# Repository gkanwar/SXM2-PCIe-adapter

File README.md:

# SXM2-PCIe-adapter

This project builds on [preliminary work](http://github.com/bbenchoff/SXM2toPCIe) by Brian Benchoff
to set up an open-hardware SXM2 to PCIe adapter module.

# Status
Board setup and impedance calculations are done. Differential pairs routing nearly finished:

# Todo list
 - [x] Set up PCB stackup consistent with JLCPCB 4-layer impedance-controlled options
 - [ ] Route differential pairs
 - [ ] Place ground vias / stitching
 - [ ] Add 12V 2x6 power management, routed into SXM directly
 - [ ] Place needed screw holes for heat sink and fan

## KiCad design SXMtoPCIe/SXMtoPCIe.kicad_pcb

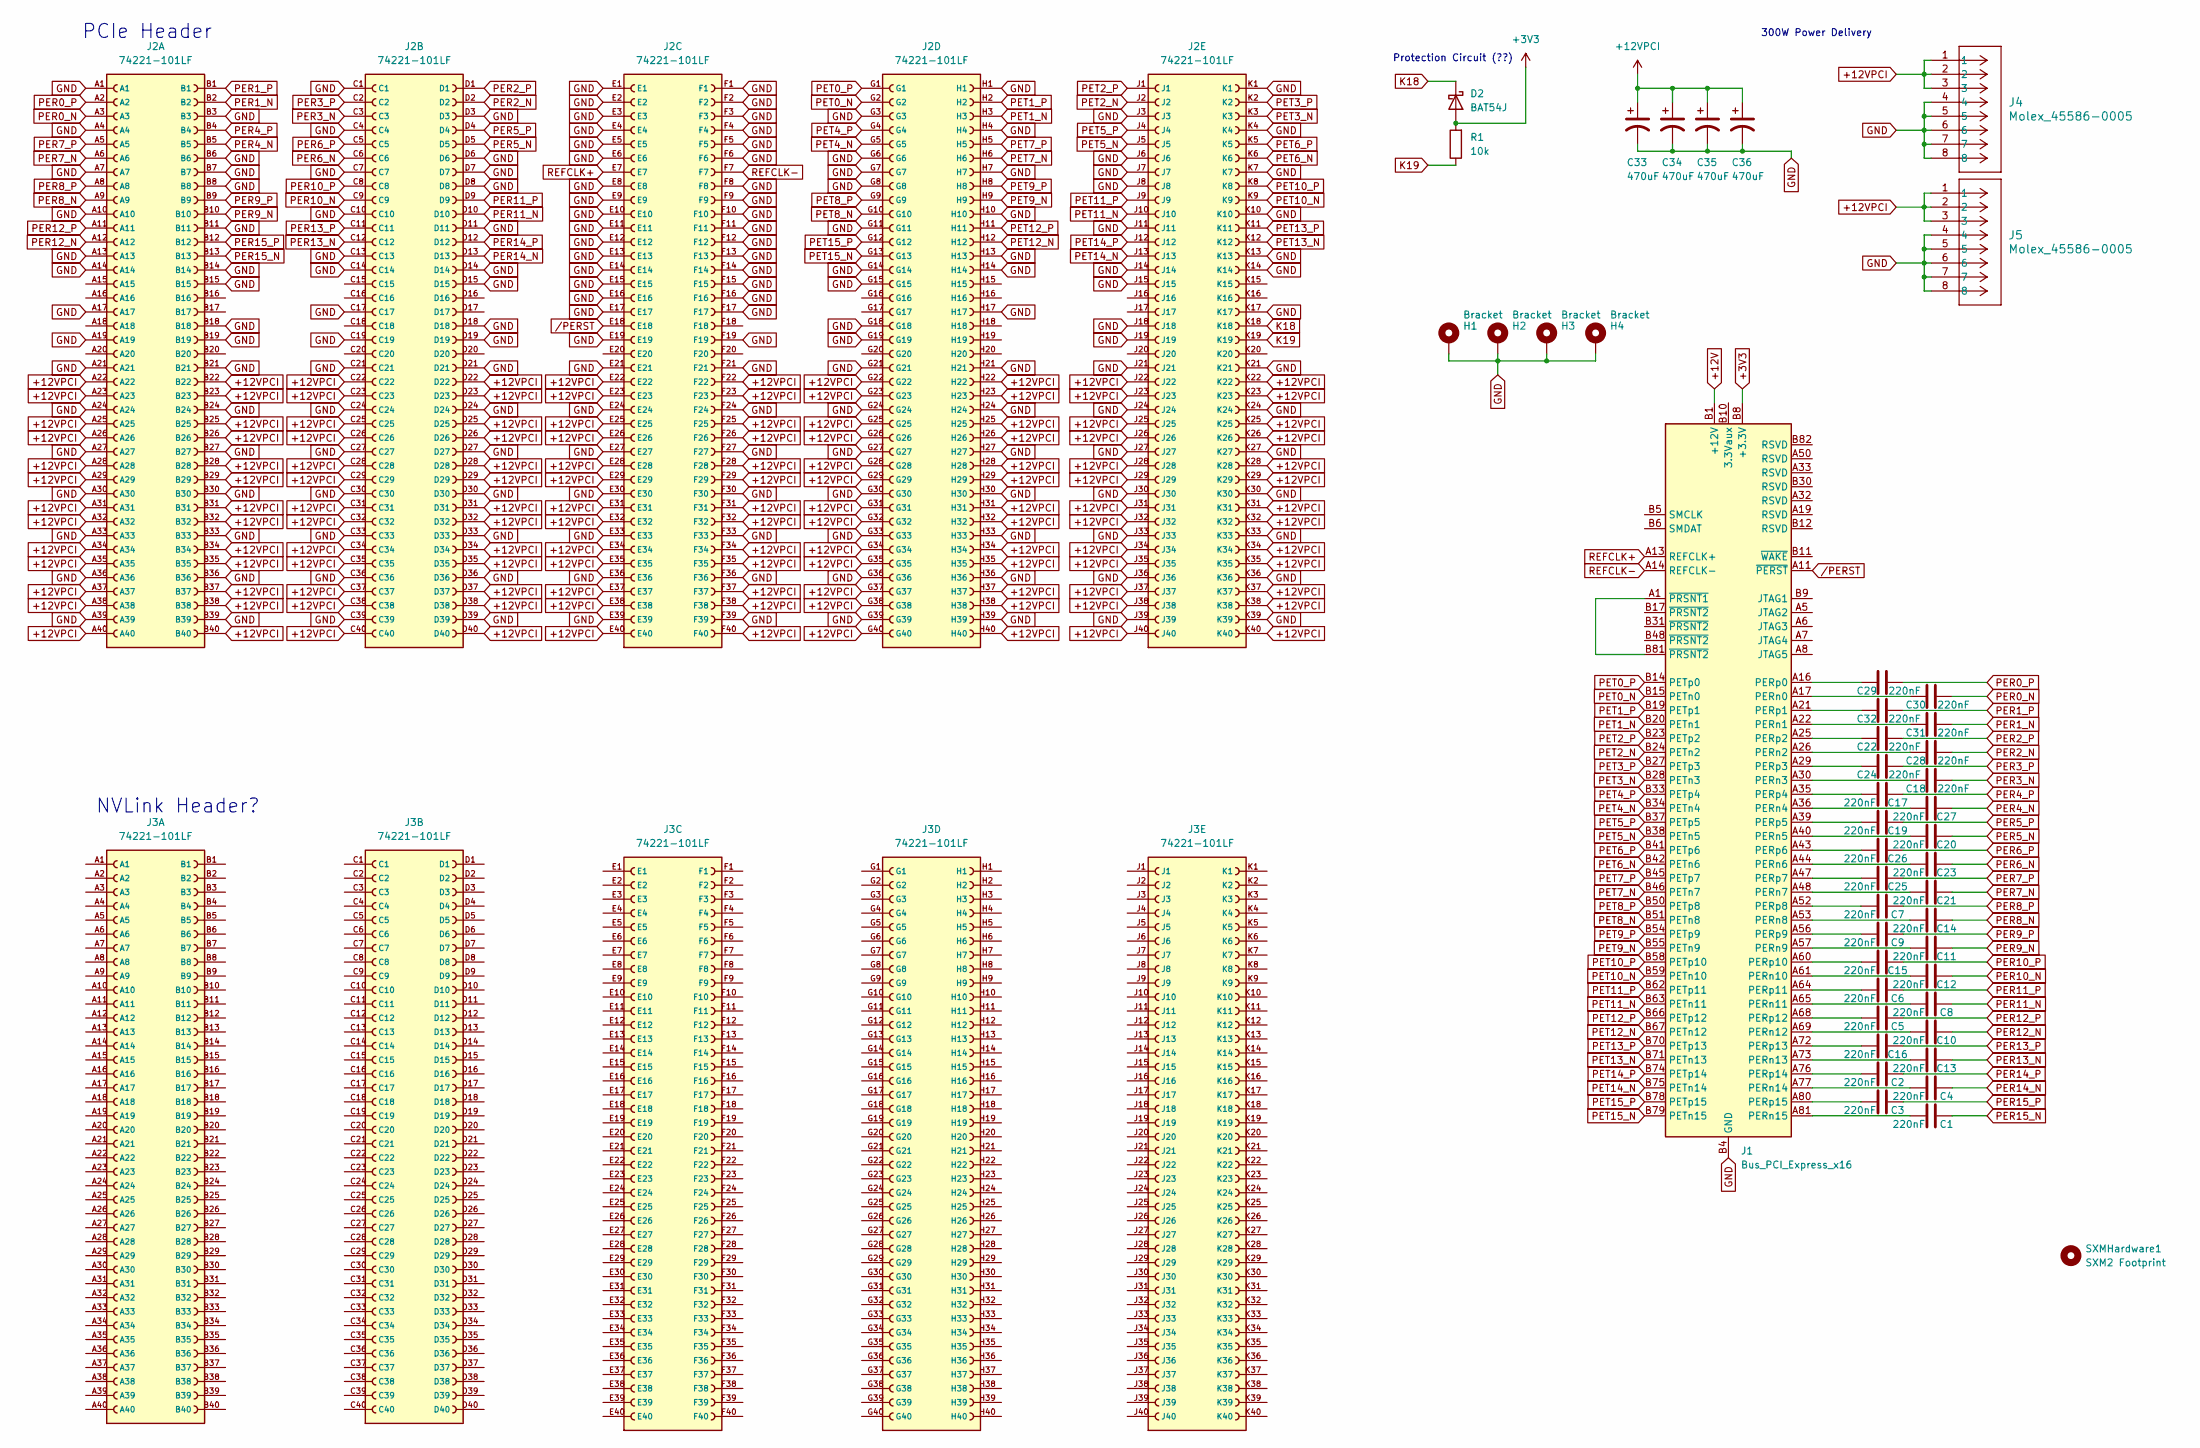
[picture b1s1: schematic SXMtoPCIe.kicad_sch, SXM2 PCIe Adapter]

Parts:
C1, C2, C3, C4, C5, C6, C7, C8, C9, C10, C11, C12, C13, C14, C15, C16, C17, C18, C19, C20, C21, C22, C23, C24, C25, C26, C27, C28, C29, C30, C31, C32: 220nF; C_0201_0603Metric_Pad0.64x0.40mm_HandSolder
C33, C34, C35, C36: 470uF; CP_Elec_6.3x7.7
D2: BAT54J; D_SOD-123
H1, H2, H3, H4: Bracket; MountingHole_3.2mm_M3_Pad_Via
J1: Bus_PCI_Express_x16; BUS_PCIexpress_x16
J2, J3: 74221-101LF; AMPHENOL_74221-101LF; PARTREV W
J4, J5: Molex_45586-0005; CONN_455860000-SD_MOL
R1: 10k; R_0402_1005Metric_Pad0.72x0.64mm_HandSolder
SXMHardware1: SXM2 Footprint; SXM2-Hardware; Digikey Part 78614040360 (times 8)

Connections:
+3V3: D2.2 (A), J1.A9 (+3.3V), J1.A10 (+3.3V), J1.B8 (+3.3V), R1.2
+12V: J1.A2 (+12V), J1.A3 (+12V), J1.B1 (+12V), J1.B2 (+12V), J1.B3 (+12V)
+12VPCI: C33.1, C34.1, C35.1, C36.1, J2.A22, J2.A23, J2.A25, J2.A26, J2.A28, J2.A29, J2.A31, J2.A32, J2.A34, J2.A35, J2.A37, J2.A38, J2.A40, J2.B22, J2.B23, J2.B25, J2.B26, J2.B28, J2.B29, J2.B31, J2.B32, J2.B34, J2.B35, J2.B37, J2.B38, J2.B40, J2.C22, J2.C23, J2.C25, J2.C26, J2.C28, J2.C29, J2.C31, J2.C32, J2.C34, J2.C35, J2.C37, J2.C38, J2.C40, J2.D22, J2.D23, J2.D25, J2.D26, J2.D28, J2.D29, J2.D31, J2.D32, J2.D34, J2.D35, J2.D37, J2.D38, J2.D40, J2.E22, J2.E23, J2.E25, J2.E26, J2.E28, J2.E29, J2.E31, J2.E32, J2.E34, J2.E35, J2.E37, J2.E38, J2.E40, J2.F22, J2.F23, J2.F25, J2.F26, J2.F28, J2.F29, J2.F31, J2.F32, J2.F34, J2.F35, J2.F37, J2.F38, J2.F40, J2.G22, J2.G23, J2.G25, J2.G26, J2.G28, J2.G29, J2.G31, J2.G32, J2.G34, J2.G35, J2.G37, J2.G38, J2.G40, J2.H22, J2.H23, J2.H25, J2.H26, J2.H28, J2.H29, J2.H31, J2.H32, J2.H34, J2.H35, J2.H37, J2.H38, J2.H40, J2.J22, J2.J23, J2.J25, J2.J26, J2.J28, J2.J29, J2.J31, J2.J32, J2.J34, J2.J35, J2.J37, J2.J38, J2.J40, J2.K22, J2.K23, J2.K25, J2.K26, J2.K28, J2.K29, J2.K31, J2.K32, J2.K34, J2.K35, J2.K37, J2.K38, J2.K40, J4.1, J4.2, J4.3, J5.1, J5.2, J5.3
GND: C33.2, C34.2, C35.2, C36.2, H1.1 (1_1), H2.1 (1_1), H3.1 (1_1), H4.1 (1_1), J1.A4 (GND), J1.A12 (GND), J1.A15 (GND), J1.A18 (GND), J1.A20 (GND), J1.A23 (GND), J1.A24 (GND), J1.A27 (GND), J1.A28 (GND), J1.A31 (GND), J1.A34 (GND), J1.A37 (GND), J1.A38 (GND), J1.A41 (GND), J1.A42 (GND), J1.A45 (GND), J1.A46 (GND), J1.A49 (GND), J1.A51 (GND), J1.A54 (GND), J1.A55 (GND), J1.A58 (GND), J1.A59 (GND), J1.A62 (GND), J1.A63 (GND), J1.A66 (GND), J1.A67 (GND), J1.A70 (GND), J1.A71 (GND), J1.A74 (GND), J1.A75 (GND), J1.A78 (GND), J1.A79 (GND), J1.A82 (GND), J1.B4 (GND), J1.B7 (GND), J1.B13 (GND), J1.B16 (GND), J1.B18 (GND), J1.B21 (GND), J1.B22 (GND), J1.B25 (GND), J1.B26 (GND), J1.B29 (GND), J1.B32 (GND), J1.B35 (GND), J1.B36 (GND), J1.B39 (GND), J1.B40 (GND), J1.B43 (GND), J1.B44 (GND), J1.B47 (GND), J1.B49 (GND), J1.B52 (GND), J1.B53 (GND), J1.B56 (GND), J1.B57 (GND), J1.B60 (GND), J1.B61 (GND), J1.B64 (GND), J1.B65 (GND), J1.B68 (GND), J1.B69 (GND), J1.B72 (GND), J1.B73 (GND), J1.B76 (GND), J1.B77 (GND), J1.B80 (GND), J2.A1, J2.A4, J2.A7, J2.A10, J2.A13, J2.A14, J2.A17, J2.A19, J2.A21, J2.A24, J2.A27, J2.A30, J2.A33, J2.A36, J2.A39, J2.B3, J2.B6, J2.B7, J2.B8, J2.B11, J2.B14, J2.B15, J2.B18, J2.B19, J2.B21, J2.B24, J2.B27, J2.B30, J2.B33, J2.B36, J2.B39, J2.C1, J2.C4, J2.C7, J2.C10, J2.C13, J2.C14, J2.C17, J2.C19, J2.C21, J2.C24, J2.C27, J2.C30, J2.C33, J2.C36, J2.C39, J2.D3, J2.D6, J2.D7, J2.D8, J2.D11, J2.D14, J2.D15, J2.D18, J2.D19, J2.D21, J2.D24, J2.D27, J2.D30, J2.D33, J2.D36, J2.D39, J2.E1, J2.E2, J2.E3, J2.E4, J2.E5, J2.E6, J2.E8, J2.E9, J2.E10, J2.E11, J2.E12, J2.E13, J2.E14, J2.E15, J2.E16, J2.E17, J2.E19, J2.E21, J2.E24, J2.E27, J2.E30, J2.E33, J2.E36, J2.E39, J2.F1, J2.F2, J2.F3, J2.F4, J2.F5, J2.F6, J2.F8, J2.F9, J2.F10, J2.F11, J2.F12, J2.F13, J2.F14, J2.F15, J2.F16, J2.F17, J2.F19, J2.F21, J2.F24, J2.F27, J2.F30, J2.F33, J2.F36, J2.F39, J2.G3, J2.G6, J2.G7, J2.G8, J2.G11, J2.G14, J2.G15, J2.G18, J2.G19, J2.G21, J2.G24, J2.G27, J2.G30, J2.G33, J2.G36, J2.G39, J2.H1, J2.H4, J2.H7, J2.H10, J2.H13, J2.H14, J2.H17, J2.H21, J2.H24, J2.H27, J2.H30, J2.H33, J2.H36, J2.H39, J2.J3, J2.J6, J2.J7, J2.J8, J2.J11, J2.J14, J2.J15, J2.J18, J2.J19, J2.J21, J2.J24, J2.J27, J2.J30, J2.J33, J2.J36, J2.J39, J2.K1, J2.K4, J2.K7, J2.K10, J2.K13, J2.K14, J2.K17, J2.K21, J2.K24, J2.K27, J2.K30, J2.K33, J2.K36, J2.K39, J4.4, J4.5, J4.6, J4.7, J4.8, J5.4, J5.5, J5.6, J5.7, J5.8
K18: D2.1 (K), J2.K18
K19: J2.K19, R1.1
unnamed: C30.2, J1.A17 (PERn0)
unnamed: C31.2, J1.A22 (PERn1)
unnamed: C28.2, J1.A26 (PERn2)
unnamed: C18.2, J1.A30 (PERn3)
unnamed: C27.1, J1.A36 (PERn4)
unnamed: C20.1, J1.A40 (PERn5)
unnamed: C23.1, J1.A44 (PERn6)
unnamed: C21.1, J1.A48 (PERn7)
unnamed: C14.1, J1.A53 (PERn8)
unnamed: C11.1, J1.A57 (PERn9)
unnamed: C12.1, J1.A61 (PERn10)
unnamed: C8.1, J1.A65 (PERn11)
unnamed: C10.1, J1.A69 (PERn12)
unnamed: C13.1, J1.A73 (PERn13)
unnamed: C4.1, J1.A77 (PERn14)
unnamed: C1.1, J1.A81 (PERn15)
unnamed: C29.2, J1.A16 (PERp0)
unnamed: C32.2, J1.A21 (PERp1)
unnamed: C22.2, J1.A25 (PERp2)
unnamed: C24.2, J1.A29 (PERp3)
unnamed: C17.1, J1.A35 (PERp4)
unnamed: C19.1, J1.A39 (PERp5)
unnamed: C26.1, J1.A43 (PERp6)
unnamed: C25.1, J1.A47 (PERp7)
unnamed: C7.1, J1.A52 (PERp8)
unnamed: C9.1, J1.A56 (PERp9)
unnamed: C15.1, J1.A60 (PERp10)
unnamed: C6.1, J1.A64 (PERp11)
unnamed: C5.1, J1.A68 (PERp12)
unnamed: C16.1, J1.A72 (PERp13)
unnamed: C2.1, J1.A76 (PERp14)
unnamed: C3.1, J1.A80 (PERp15)
unnamed: J1.A1 (~PRSNT1), J1.B81 (~PRSNT2)
PER0_N: C30.1, J2.A3
PER0_P: C29.1, J2.A2
PER1_N: C31.1, J2.B2
PER1_P: C32.1, J2.B1
PER2_N: C28.1, J2.D2
PER2_P: C22.1, J2.D1
PER3_N: C18.1, J2.C3
PER3_P: C24.1, J2.C2
PER4_N: C27.2, J2.B5
PER4_P: C17.2, J2.B4
PER5_N: C20.2, J2.D5
PER5_P: C19.2, J2.D4
PER6_N: C23.2, J2.C6
PER6_P: C26.2, J2.C5
PER7_N: C21.2, J2.A6
PER7_P: C25.2, J2.A5
PER8_N: C14.2, J2.A9
PER8_P: C7.2, J2.A8
PER9_N: C11.2, J2.B10
PER9_P: C9.2, J2.B9
PER10_N: C12.2, J2.C9
PER10_P: C15.2, J2.C8
PER11_N: C8.2, J2.D10
PER11_P: C6.2, J2.D9
PER12_N: C10.2, J2.A12
PER12_P: C5.2, J2.A11
PER13_N: C13.2, J2.C12
PER13_P: C16.2, J2.C11
PER14_N: C4.2, J2.D13
PER14_P: C2.2, J2.D12
PER15_N: C1.2, J2.B13
PER15_P: C3.2, J2.B12
PET0_N: J1.B15 (PETn0), J2.G2
PET0_P: J1.B14 (PETp0), J2.G1
PET1_N: J1.B20 (PETn1), J2.H3
PET1_P: J1.B19 (PETp1), J2.H2
PET2_N: J1.B24 (PETn2), J2.J2
PET2_P: J1.B23 (PETp2), J2.J1
PET3_N: J1.B28 (PETn3), J2.K3
PET3_P: J1.B27 (PETp3), J2.K2
PET4_N: J1.B34 (PETn4), J2.G5
PET4_P: J1.B33 (PETp4), J2.G4
PET5_N: J1.B38 (PETn5), J2.J5
PET5_P: J1.B37 (PETp5), J2.J4
PET6_N: J1.B42 (PETn6), J2.K6
PET6_P: J1.B41 (PETp6), J2.K5
PET7_N: J1.B46 (PETn7), J2.H6
PET7_P: J1.B45 (PETp7), J2.H5
PET8_N: J1.B51 (PETn8), J2.G10
PET8_P: J1.B50 (PETp8), J2.G9
PET9_N: J1.B55 (PETn9), J2.H9
PET9_P: J1.B54 (PETp9), J2.H8
PET10_N: J1.B59 (PETn10), J2.K9
PET10_P: J1.B58 (PETp10), J2.K8
PET11_N: J1.B63 (PETn11), J2.J10
PET11_P: J1.B62 (PETp11), J2.J9
PET12_N: J1.B67 (PETn12), J2.H12
PET12_P: J1.B66 (PETp12), J2.H11
PET13_N: J1.B71 (PETn13), J2.K12
PET13_P: J1.B70 (PETp13), J2.K11
PET14_N: J1.B75 (PETn14), J2.J13
PET14_P: J1.B74 (PETp14), J2.J12
PET15_N: J1.B79 (PETn15), J2.G13
PET15_P: J1.B78 (PETp15), J2.G12
REFCLK+: J1.A13 (REFCLK+), J2.E7
REFCLK-: J1.A14 (REFCLK-), J2.F7
/PERST: J1.A11 (~PERST), J2.E18

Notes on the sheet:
Protection Circuit (??)
NVLink Header?
300W Power Delivery
PCIe Header

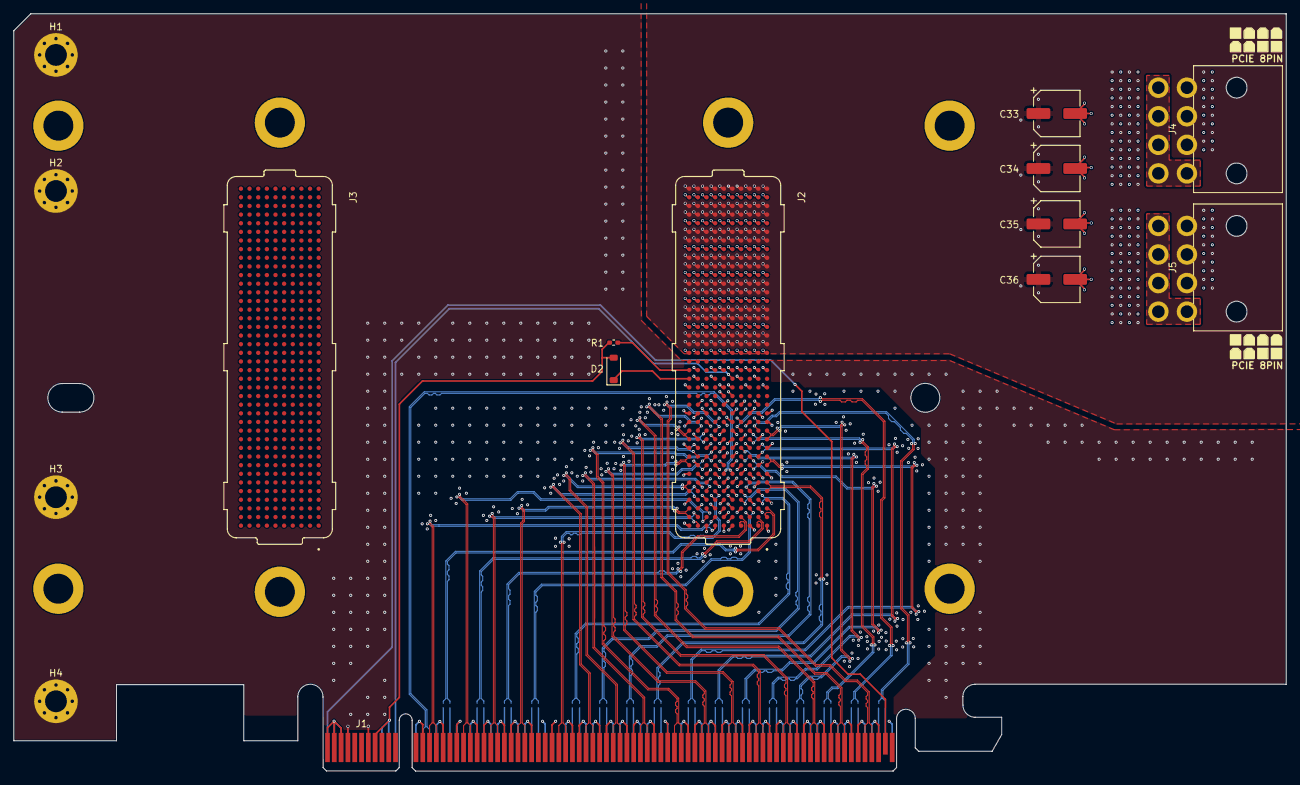
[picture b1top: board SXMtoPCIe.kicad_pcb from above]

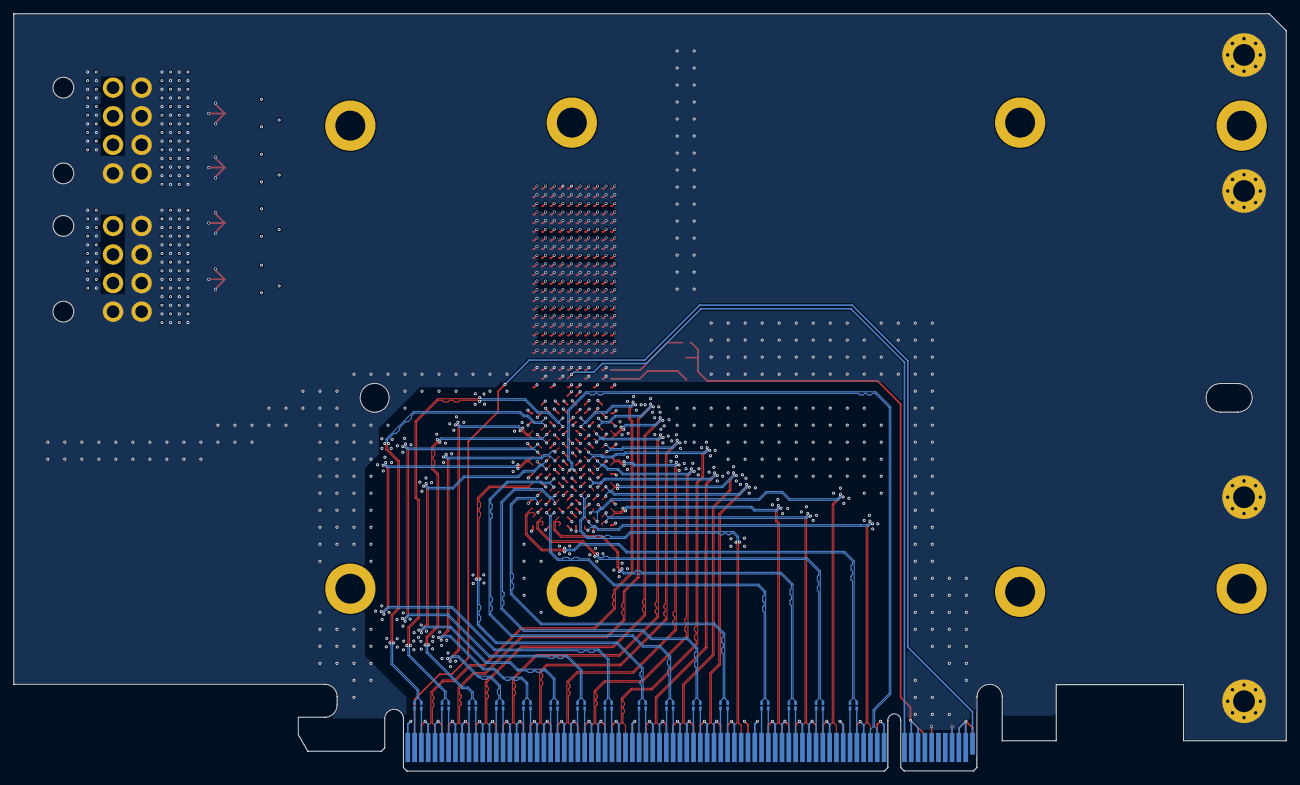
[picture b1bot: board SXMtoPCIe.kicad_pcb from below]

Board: 4 copper layers, 187.0 x 111.3 mm, 48 parts (32 on the bottom side), 106 nets.

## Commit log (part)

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2025-06-02 Everything
2025-09-22 save
